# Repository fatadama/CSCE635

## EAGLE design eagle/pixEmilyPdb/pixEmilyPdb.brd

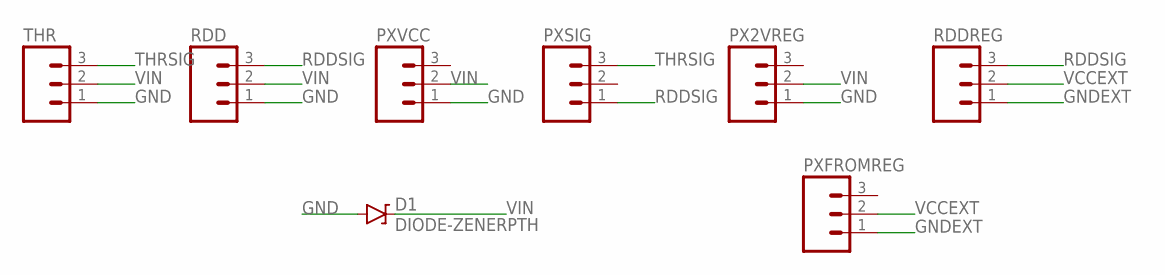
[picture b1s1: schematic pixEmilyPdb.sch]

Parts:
D1: DIODE-ZENERPTH; DIODE-ZENER
PX2VREG: M03PTH; 1X03
PXFROMREG: M03PTH; 1X03
PXSIG: M03PTH; 1X03
PXVCC: M03PTH; 1X03
RDD: M03PTH; 1X03
RDDREG: M03PTH; 1X03
THR: M03PTH; 1X03

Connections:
GND: D1.P$2 (A), PX2VREG.1, PXVCC.1, RDD.1, THR.1
GNDEXT: PXFROMREG.1, RDDREG.1
RDDSIG: PXSIG.1, RDD.3, RDDREG.3
THRSIG: PXSIG.3, THR.3
VCCEXT: PXFROMREG.2, RDDREG.2
VIN: D1.P$1 (C), PX2VREG.2, PXVCC.2, RDD.2, THR.2

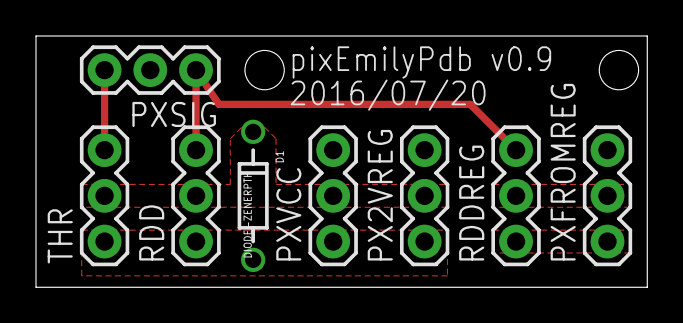
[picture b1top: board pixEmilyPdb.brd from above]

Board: 2 copper layers, 34.0 x 14.0 mm, 8 parts (0 on the bottom side), 6 nets.

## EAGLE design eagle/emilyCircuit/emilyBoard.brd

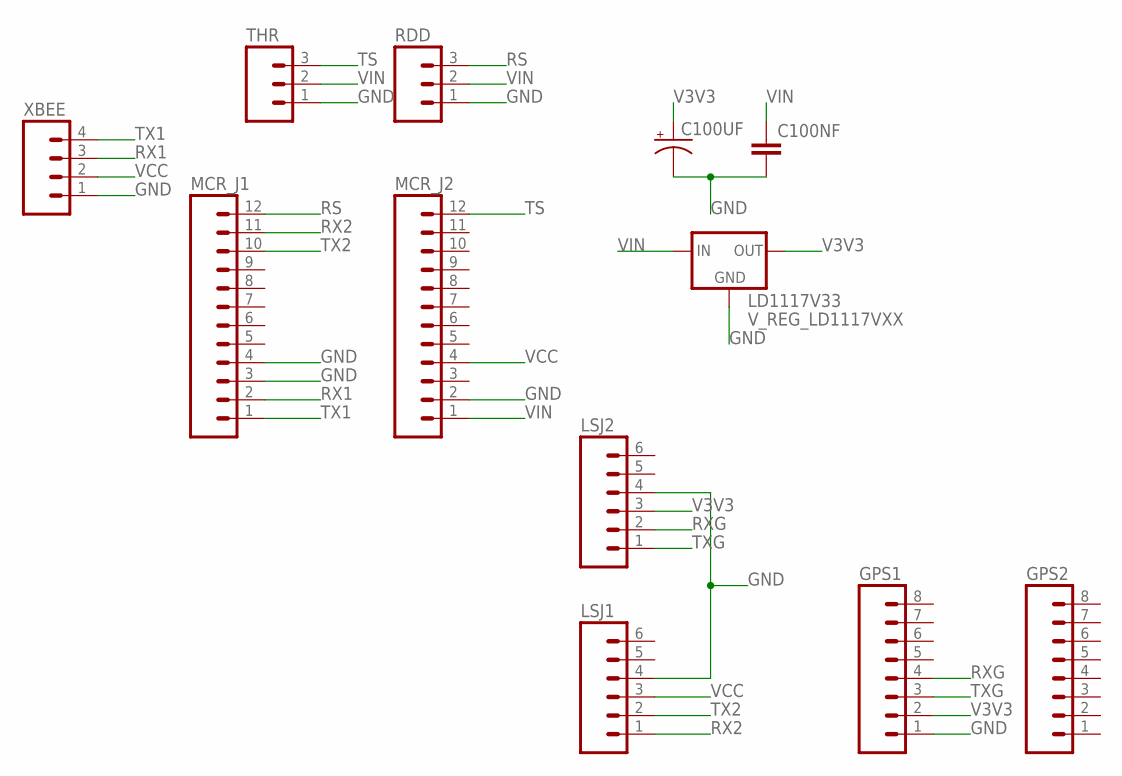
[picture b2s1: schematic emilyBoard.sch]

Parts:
C100NF: CAPEZ; CAP-PTH-SMALLEZ
C100UF: CAP_POLPTH1; CPOL-RADIAL-100UF-25V
GPS1, GPS2: M08; 1X08_ROUND
LD1117V33: V_REG_LD1117VXX; 78XXL
LSJ1, LSJ2: M06NO_SILK_FEMALE_PTH; 1X06_NO_SILK
MCR_J1, MCR_J2: M12PTH; 1X12
RDD: M03PTH; 1X03
THR: M03PTH; 1X03
XBEE: M04PTH; 1X04

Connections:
GND: C100NF.2, C100UF.2 (-), GPS1.1, LD1117V33.IN (GND), LSJ1.4, LSJ2.4, MCR_J1.3, MCR_J1.4, MCR_J2.2, RDD.1, THR.1, XBEE.1
RS: MCR_J1.12, RDD.3
RX1: MCR_J1.2, XBEE.3
RX2: LSJ1.1, MCR_J1.11
RXG: GPS1.4, LSJ2.2
TS: MCR_J2.12, THR.3
TX1: MCR_J1.1, XBEE.4
TX2: LSJ1.2, MCR_J1.10
TXG: GPS1.3, LSJ2.1
V3V3: C100UF.1 (+), GPS1.2, LD1117V33.GND (OUT), LSJ2.3
VCC: LSJ1.3, MCR_J2.4, XBEE.2
VIN: C100NF.1, LD1117V33.OUT (IN), MCR_J2.1, RDD.2, THR.2

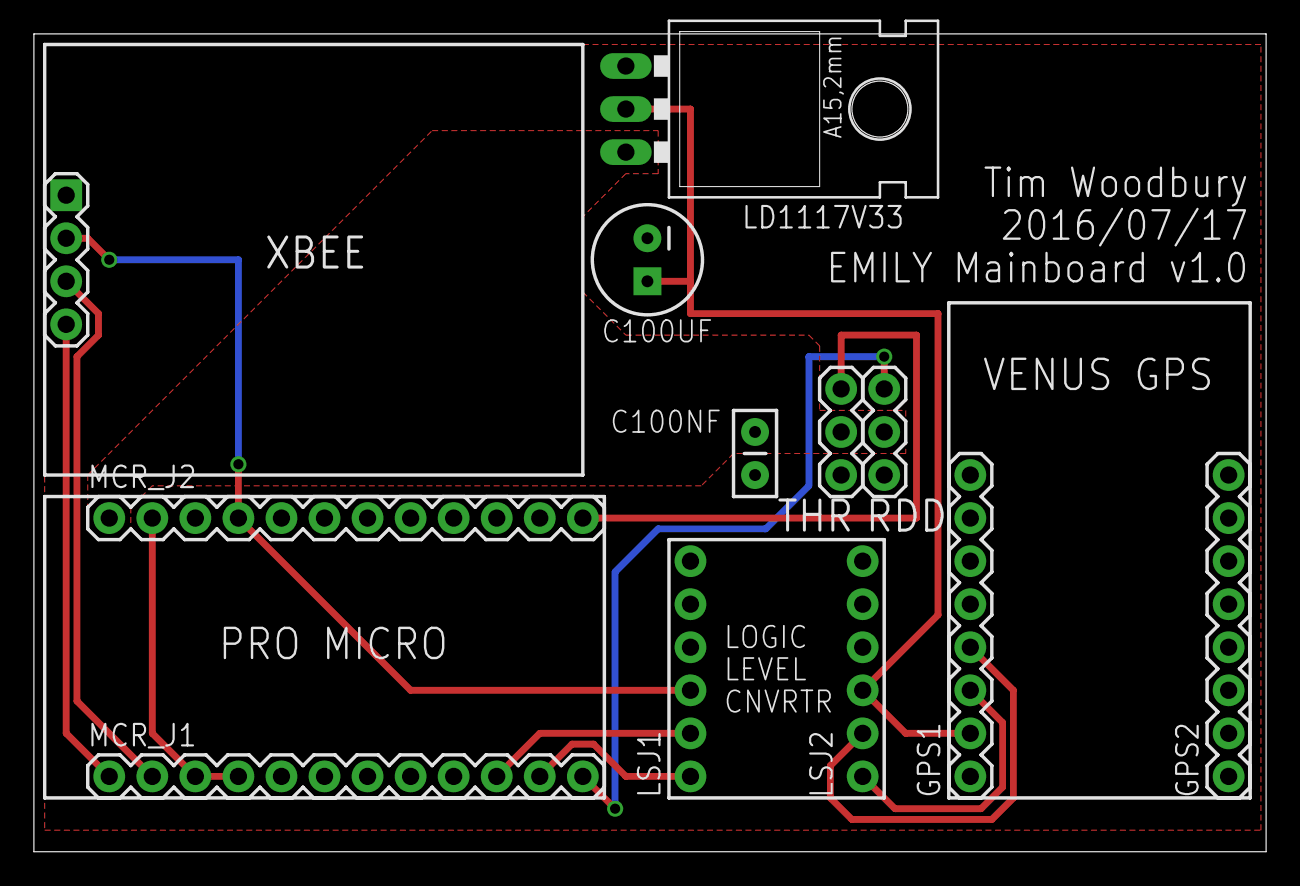
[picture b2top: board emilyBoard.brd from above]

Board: 2 copper layers, 72.7 x 48.2 mm, 12 parts (0 on the bottom side), 12 nets.

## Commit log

2016-04-14 Added low pass filter object for smoothing control signals from ground. TODO use this class to update the GPS processing. TODO read heading and speed from GPS GPRMC messages
2016-04-15 Added parsing of speed and heading in standard GPS messages. Not sure if it will work.
2016-04-15 Broke out low pass filter class into own source code. Added test function to validate that PID seems to be working correctly.
2016-04-16 There's some kind of error or memory leak in emily_driver. It causes the system to fail (stop transmitting debug messages) after a short amount of time when the PWM writing and XBee communications ar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
2016-04-17 Modified the GPS object to have a local gpsData object instead of a status object. Call sync() function to put the local gps value into the global structure. Program seems to run stably with this cha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
2016-04-17 Updated the emilyControl object to no longer use the global status object - it just uses a local copy in the misc_tasks() function
2016-04-17 Removed the global status pointer from the commParser class. TODO resolve issues with GPS data getting garbled at fast sample rates.
2016-04-17 Something is not working right. Apparently the commParser bitstring is not getting set.
2016-04-17 Added a serial debugging script for reading debugging output from the Arduino when it's on USB0
2016-04-18 There's some bitshifting error associated with how the 32 bit ints are packed in ESP. Using memcpy() seems to fix it. TODO change all such in ESP to memcpys
2016-04-18 Modified debug output from Arduino to be more parseable and added logging to serial_debugging python code Finished converting all ESP int32_t packs into memcpy() calls Added a test file for using cur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
2016-04-18 Added servo objects to the main driver to replace analogWrite() calls. Untested on servos yet.
2016-04-18 Updated serial debugging function to do error checking if board is not connected over USV|B
2016-04-19 Switched back to using old ESP library writen in python for simplicity. Newer C++ extension still exists in folder EPS
2016-04-19 Deleted old files
2016-04-19 Started adding messages to the python ESP. Have not tested with C++/Arduino yet, TODO
2016-04-19 Finished adding ESP functions to python version. Tested that GPS and control are received by Arduino
2016-04-19 Added comments to esp.py
2016-04-19 Modified emily_driver to disble all GPS messages except GPRMC types. Increased SoftwareSerial baud rate to 57k. Servo jitter seems acceptably low at this rate. Added serial_control_test.py python scr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
2016-04-21 Added a combined GPS + speed/heading message packer to ESP.h. TODO add unpacker and python version
2016-04-21 Added new GPS_POS message to ESP for sending speed and heading information. Has not been tested but it does compile. Modified gpsData object to have a gpsStatus enum member that can be set by emilyGP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
2016-04-23 Added heartbeat message to ESP C++ implementation. Added heartbeat streaming by default to commParser object.
2016-04-25 Fixed bug in commParser; compiles Modified emilyControl to map throttle from 1500 to 2000 ms. (Apprently the motor reverses) Modified python control test script to write throttle values on w/s keys
2016-04-25 Added new python files for the XBee bridge code. Development for Windows 7 on Python 3.5 using pyserial and the websockets library at: https://pypi.python.org/pypi/websockets Started some basic class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
2016-04-26 Removed redundant call to serial.open() in control test script
2016-04-27 Created bridgeProcess class for persistent memory with a while(true) loop structure for realtime process Tested that code runs and we can write to state memory and read elsewhere
2016-04-29 Renamed esp to esp_python. Apparently that name may conflict with some python modules, at least it seems to on my Ubuntu 12.04 install
2016-04-29 Removed ESP.py
2016-04-29 Started an EMILY "emulator". Will have to use UDP loopback or nanomsg to fake the serial communication
2016-04-30 Reduced the lowpass filter 'alpha' values from 0.1 to 0.05
2016-04-30 Reduced lowpass filter value
2016-05-03 Added joystick writing file and mods to ESP in python
2016-05-03 Corrected a bug where heading in radians was being ultiplied by degrees2radians conversion factor. Should be ok now? Not tested
2016-05-03 Added parser for April 30 data
2016-05-03 Added files to try to do model identification. Don't work.
2016-05-03 Added an outlier rejection function to the emilyGPS object. Has not been tested. The basic algorithm has been evaluated on data in python/matlab and rejects about 10% of data points
2016-05-04 Added a zero-jerk filter and tuned using histogram. Looks reasonable, hard to validate. Heading matches GPS output, but not velocity.
2016-05-04 Modified filter2 file to write to file
2016-05-04 Added a second matlab file for model fitting. Works better, not known if useful
2016-05-04 Added logs from 4-30 to the repository
2016-05-04 Added hardware_interface class for talking to an Xbee. Provides UDP for software-in-loop testing with the same interface. Validated with test programs. Wrote emilyEcho program to print any messages r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
2016-05-04 Added simulation, GPS sampling to emulator.
2016-05-04 Added joystick support class
2016-05-04 Removed excess checks in the acceptGps() function so we only reject based on the position and time reading
2016-05-05 Added simple keyboard input if there's no joystick, for debugging mostly Added logging Broken the message handling in xbee_bridge_process into its own function Added control_mode flag Added some comm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
2016-05-05 Added readme describing install proccedure for nanomsg-python on windows, since this required extraa work
2016-05-05 Added logging of serial messages in espParser object, tested. Fixed an issue in the parser that might have been causing it to throw away some bytes when it shouldn't have, but I'm not sure if this ha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
2016-05-05 Added settings file to set the comm port of the XBee and toggle SIL mode on/off. Validated parser. Fixed bug in hardware_interface object
2016-05-05 Added bassic control object to xbee_bridge suite. Need to add PID and incorporate with main code
2016-05-05 Started a nanomsg example but didn't get far. TODO do this later
2016-05-05 Added PID class from old Crazyflie files Creates a log Added control object to main xbee_bridge process but did not test yet
2016-05-06 Added many things to get ready to test waypoint navigation. Added EKF to xbee_bridge_state based on data from last trial Added debugging interface for generating synthetic waypoints to EMILY on the f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
2016-05-06 Corrected misaligned braces in *cpp
2016-05-06 Some random hacks to try to reject GPS correctly on the ground side
2016-05-06 Changed GPS stream rate to 10 Hz
2016-05-06 Minor changes to Arduin firmware
2016-05-06 Fixed a bug where the GPS velocity and heading were getting rescaled twice, causing bad unit outputs.
2016-05-06 Added logging to synethetic waypoint Misc bugfixed from testing Modified settings
2016-05-06 Added matlab script to process data in post
2016-05-06 Added logging to synthetic waypoint object. Made the speed in turning mode and cruising mode under automatic control a settings parameter. Tested in SIL.
2016-05-06 Modified automatic control mode. EMILY will turn on the throttle until a smoothed average of throttle exceeds a threshold of 0.25, THEN will create synthetic waypoint. This is supposed to make the he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
2016-05-06 Fixed a bug where the gpsStatus object in main() was never getting set to a new value
2016-05-06 Removed matlab backup file
2016-05-06 Commit changes from testing
2016-05-07 Changes from testing. Need to improve heading detection.
2016-05-07 Bug fix from testing
2016-05-07 Added new test sketch to evaluate GPS checksum
2016-05-07 Added checksum parsing to GPS messages. Tested in Arduino file emily_gps_checksum. TODO integrate with main code and confirm.
2016-05-07 Turned off debugging in emily_driver sketch. Integrated GPS with checksumming. Need to test if working.
2016-05-07 Modified pfields mode significantly. When triggered, a fixed-action pattern of five second throttle-on is engaged to get the heading. We record position at the start and end of this mode as a backup 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
2016-05-07 Changed GPS stream to prevent sending a message if we don't have new GPS
2016-05-07 Modified xbee_bridge main() to write a copy of the settings to an INI file in the log folder on each run for future testing.
2016-05-07 Modified xbee_bridge_state to use the GPS speed and heading directly without filtering. GPS heading seems to be better than the lowpassed approximations were.
2016-05-07 Improved file for parsing logs in MATLAB Added python script to parse through directly and determine which log directories have an empty controlObject log file, for quickly determining which log case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
2016-05-07 Minor changes to MATLAB file.
2016-05-08 Added basic library for unpacking nanomsg buffers to get simple messages. Uses a four-character message id with comma-separated values.
2016-05-08 Addedd Jesus's pfields code into a library
2016-05-08 Renamed msgParser folder to match library name
2016-05-08 Commits from testing. ADded message for sending reference speed. Added new file, pfield_realtime, for the realtime pfields implementation
2016-05-08 Modified nanomsg example to use the ipcPacker library for talking to the C++ test file
2016-05-08 Added interprocess communciation object. Began integrating with the main code.
2016-05-08 Hacked the pfields with a range scaling factor within 10 meters to try to get it to stop.
2016-05-08 Tried to add *.ini logs to .gitignore
2016-05-08 Added MATLAB processing files
2016-05-09 Added abilityto load waypoints from file. TODO cycle through waypoints
2016-05-09 Added support for looping over waypoints forever
2016-05-10 Added websocket server standalone file to xbee bridge. Run it to enable interprocess communication.
2016-05-10 Modified the bridge to support the hacky websocket interface
2016-05-10 Made a spreadsheet for computing and graphing local coordinates near a designated GPS "home"
2016-05-20 Updated gitignore to include temporary/unneeded eagle files
2016-05-20 Added EAGLE drawings of the basic circuit for PCB
2016-05-23 Added connections to emily board
2016-06-06 Quick hack to remove nanomsg dependencies and use UDP sockets instead
2016-06-12 Updated post-processing files
2016-07-17 Updated EMILY PCB files with labels. Complies with OSHPark DRGs and Eagle ERGs.
2016-07-20 Added power distribution board for EMILY using Pixhawk
2016-07-21 Updated PBD with mounting holes & misc fixes

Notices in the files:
parts and their libraries:
SparkFun-Capacitors: Licensing: Creative Commons ShareAlike 4.0 International - https://creativecommons.org/licenses/by-sa/4.0
